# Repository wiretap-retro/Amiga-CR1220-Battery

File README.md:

# Amiga CR1220 Battery
A small CR1220/1225 battery holder for the Amiga and other boards.

## Info
This is a simple Amiga battery replacement design based on dec0de Consulting / LinuxJedi's design, but with a slightly smaller footprint and added test points for voltage measurement. 

## Parts Needed
* The circuit board, from your fabricator of choice. (JLCPCB, PCBway, OSH Park, etc.)
* Renata SMTU1220-LF or SMTU1225-LF battery holder, depending which battery you want to use
* Infineon IRLML6402 or IRLML6401 P-channel MOSFET (SOT-23)
* 3x 1x1-pin 2.54mm male pin headers
* CR1220 or CR1225 battery

## Assembly
* Solder Q1 to the back side of the board.
* Install a single through-hole 2.54mm male pin header on the bottom of the narrow end of the board and flush clip it, then solder.
* Install the battery holder to the SMD pads, paying attention to orientation.
* Install the other two 2.54mm male pin headers to the bottom side of the board and solder them.
* Install the CR1220 / CR1225 battery
* Solder it into your motherboard or expansion card

## Other
Link to dec0de Consulting CR2032 version: https://gitlab.com/dec0de-consulting/amiga-cr2032

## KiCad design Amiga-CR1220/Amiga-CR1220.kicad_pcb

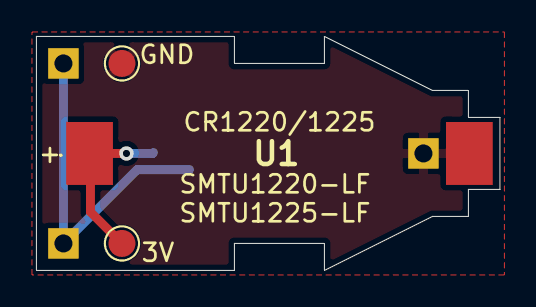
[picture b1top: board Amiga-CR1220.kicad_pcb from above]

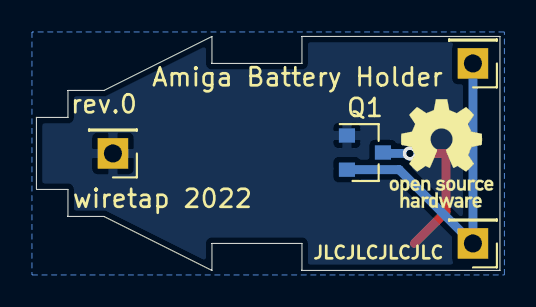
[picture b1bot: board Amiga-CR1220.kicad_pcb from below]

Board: 2 copper layers, 25.8 x 13.0 mm, 7 parts (4 on the bottom side), 3 nets.

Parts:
3V: TestPoint_3V; TestPoint_Pad_D1.5mm
GND: TestPoint_GND; TestPoint_Pad_D1.5mm
J1, J2, J3: Conn_01x01_Male; PinHeader_1x01_P2.54mm_Vertical
Q1: IRLML6402; SOT-23
U1: SMTU1220-LF; SMTU1225LF

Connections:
+3V0: 3V.1, Q1.3, U1.1
GND: GND.1, J3.1, Q1.1, U1.2
unnamed: J1.1, J2.1, Q1.2
